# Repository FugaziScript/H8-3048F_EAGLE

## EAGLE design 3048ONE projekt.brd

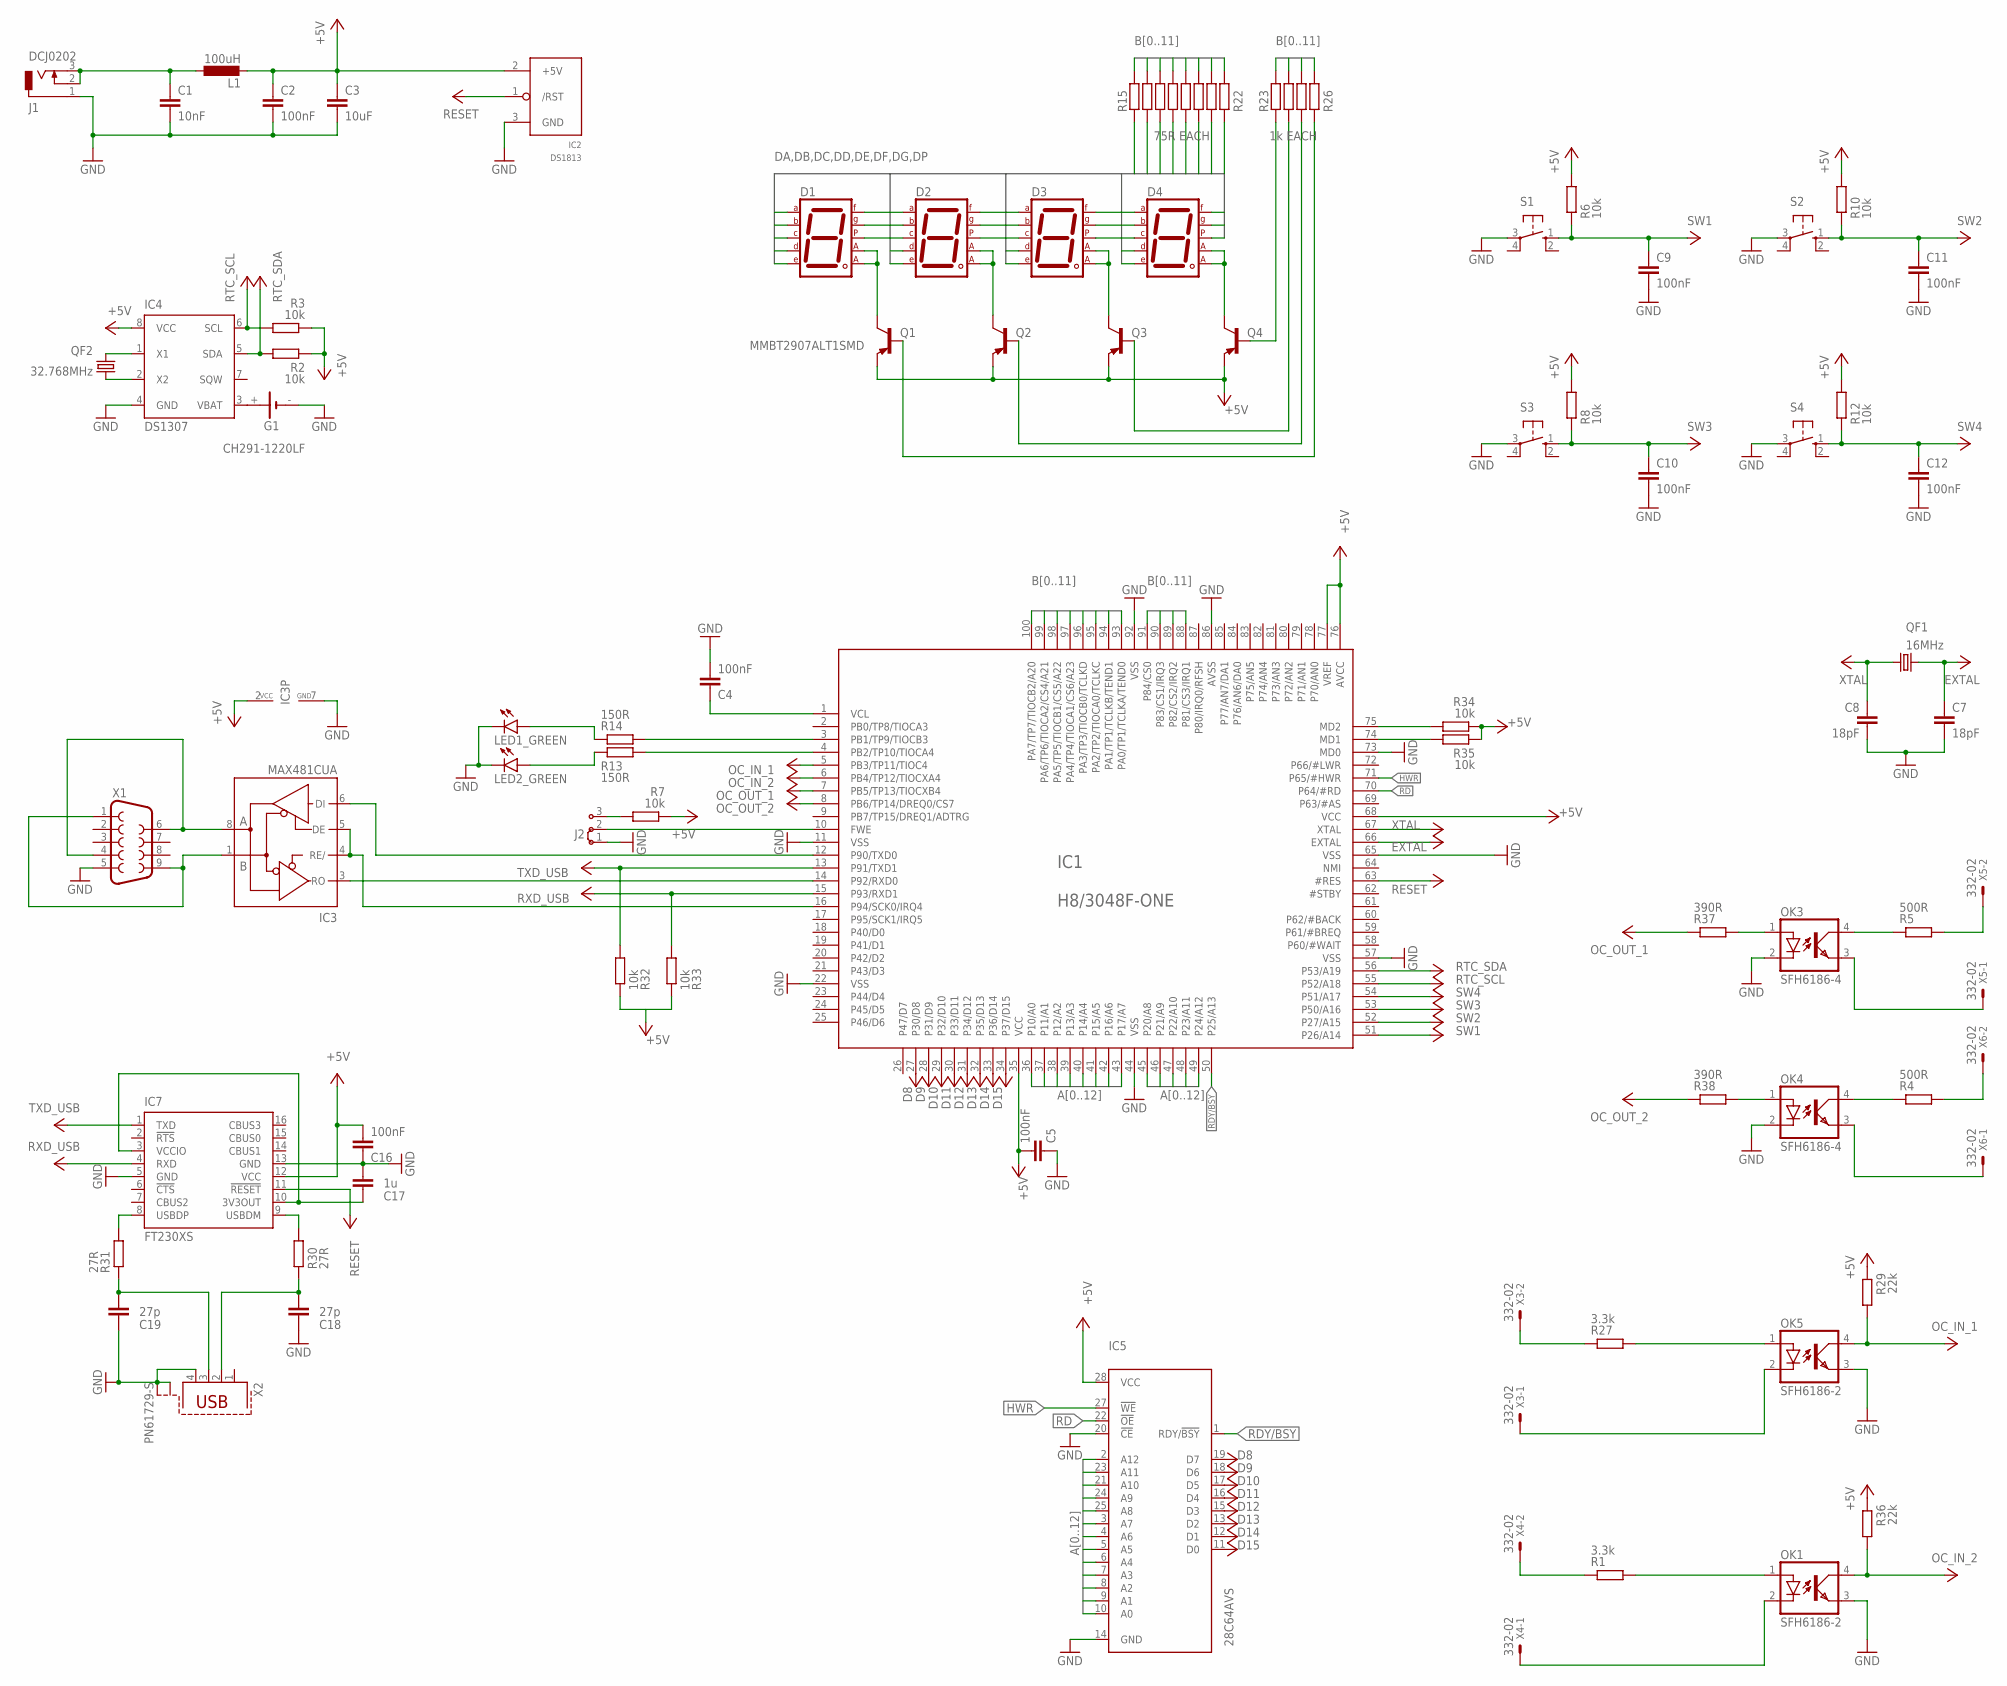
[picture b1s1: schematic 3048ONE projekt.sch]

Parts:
C1: 10nF; C0805
C2, C4, C5, C9, C10, C11, C12, C16: 100nF; C0805
C3: 10uF; C0805
C7, C8: 18pF; C0805
C17: 1u; C0805
C18, C19: 27p; C0805
D1, D2, D3, D4: 7SEG-CA; 7SEG-13
G1: CH291-1220LF
IC1: H8/3048F-ONE; TQFP100-16X16
IC2: DS1813; TO-92
IC3: MAX481CUA; UMAX8
IC4: DS1307; DIL08
IC5: 28C64AVS; VSOP28-8X13
IC7: FT230XS; SSOP16
J1: DCJ0202
J2: J2X2MM; 04C
L1: 100uH; PIS2816
LED1_GREEN, LED2_GREEN: LED3MM
OK1, OK5: SFH6186-2; SMD4-7
OK3, OK4: SFH6186-4; SMD4-7
Q1, Q2, Q3, Q4: MMBT2907ALT1SMD; SOT23-BEC
QF1: 16MHz; CTS406
QF2: 32.768MHz; CTS406
R1, R27: 3.3k; M0805
R2, R3, R6, R7, R8, R10, R12, R32, R33, R34, R35: 10k; M0805
R4, R5: 500R; M0805
R13, R14, R15, R16, R17, R18, R19, R20, R21, R23, R24, R25: 150R; M0805
R22: 75R EACH; M0805
R26: 1k EACH; M0805
R29, R36: 22k; M0805
R30, R31: 27R; M0805
R37, R38: 390R; M0805
S1, S2, S3, S4: 40-XX; B3F-40XX
X1: F09HP
X2: PN61729-S
X3, X4, X5, X6: 332-02

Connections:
+5V: C2.1, C3.1, C5.2, C16.2, IC1.35 (VCC), IC1.68 (VCC), IC1.76 (AVCC), IC1.77 (VREF), IC2.2 (+5V), IC3.2 (VCC), IC4.8 (VCC), IC5.28 (VCC), IC7.12 (VCC), L1.2, Q1.E, Q2.E, Q3.E, Q4.E, R2.1, R3.1, R6.2, R7.1, R8.2, R10.2, R12.2, R29.1, R34.1, R35.1, R36.1
A0: IC1.38 (P12/A2), IC5.10 (A0)
A1: IC1.37 (P11/A1), IC5.9 (A1)
A2: IC1.36 (P10/A0), IC5.8 (A2)
A3: IC1.49 (P24/A12), IC5.7 (A3)
A4: IC1.48 (P23/A11), IC5.6 (A4)
A5: IC1.47 (P22/A10), IC5.5 (A5)
A6: IC1.46 (P21/A9), IC5.4 (A6)
A7: IC1.45 (P20/A8), IC5.3 (A7)
A8: IC1.42 (P16/A6), IC5.25 (A8)
A9: IC1.41 (P15/A5), IC5.24 (A9)
A10: IC1.39 (P13/A3), IC5.21 (A10)
A11: IC1.40 (P14/A4), IC5.23 (A11)
A12: IC1.43 (P17/A7), IC5.2 (A12)
B0: IC1.100 (PA7/TP7/TIOCB2/A20), R15.1
B1: IC1.99 (PA6/TP6/TIOCA2/CS4/A21), R16.1
B2: IC1.98 (PA5/TP5/TIOCB1/CS5/A22), R17.1
B3: IC1.97 (PA4/TP4/TIOCA1/CS6/A23), R18.1
B4: IC1.96 (PA3/TP3/TIOCB0/TCLKD), R19.1
B5: IC1.95 (PA2/TP2/TIOCA0/TCLKC), R20.1
B6: IC1.94 (PA1/TP1/TCLKB/TEND1), R21.1
B7: IC1.93 (PA0/TP1/TCLKA/TEND0), R22.1
B8: IC1.91 (P84/CS0), R23.1
B9: IC1.90 (P83/CS1/IRQ3), R24.1
B10: IC1.89 (P82/CS2/IRQ2), R25.1
B11: IC1.88 (P81/CS3/IRQ1), R26.1
D8: IC1.27 (P30/D8), IC5.19 (D7)
D9: IC1.28 (P31/D9), IC5.18 (D6)
D10: IC1.29 (P32/D10), IC5.17 (D5)
D11: IC1.30 (P33/D11), IC5.16 (D4)
D12: IC1.31 (P34/D12), IC5.15 (D3)
D13: IC1.32 (P35/D13), IC5.13 (D2)
D14: IC1.33 (P36/D14), IC5.12 (D1)
D15: IC1.34 (P37/D15), IC5.11 (D0)
DA: D1.7 (A), D2.7 (A), D3.7 (A), D4.7 (A), R19.2
DB: D1.6 (B), D2.6 (B), D3.6 (B), D4.6 (B), R21.2
DC: D1.4 (C), D2.4 (C), D3.4 (C), D4.4 (C), R20.2
DD: D1.2 (D), D2.2 (D), D3.2 (D), D4.2 (D), R18.2
DE: D1.1 (E), D2.1 (E), D3.1 (E), D4.1 (E), R17.2
DF: D1.9 (F), D2.9 (F), D3.9 (F), D4.9 (F), R16.2
DG: D1.10 (G), D2.10 (G), D3.10 (G), D4.10 (G), R15.2
DP: D1.5 (DP), D2.5 (DP), D3.5 (DP), D4.5 (DP), R22.2
EXTAL: C7.1, IC1.66 (EXTAL), QF1.3 (2)
GND: C1.2, C2.2, C3.2, C4.2, C5.1, C7.2, C8.2, C9.2, C10.2, C11.2, C12.2, C16.1, C17.2, C18.1, C19.1, G1.-, IC1.11 (VSS), IC1.22 (VSS), IC1.44 (VSS), IC1.57 (VSS), IC1.65 (VSS), IC1.73 (MD0), IC1.86 (AVSS), IC1.92 (VSS), IC2.3 (GND), IC3.7 (GND), IC4.4 (GND), IC5.14 (GND), IC5.20 (!CE), IC7.5 (GND), IC7.13 (GND), J1.1, J2.1, LED1_GREEN.K (C), LED2_GREEN.K (C), OK1.3 (EMIT), OK3.2 (C), OK4.2 (C), OK5.3 (EMIT), S1.3, S2.3, S3.3, S4.3, X1.5, X2.4, X2.S1, X2.S2
HWR: IC1.71 (P65/#HWR), IC5.27 (!WE)
unnamed: IC1.10 (FWE), J2.2
unnamed: C1.1, J1.2, J1.3, L1.1
unnamed: IC3.1 (B), X1.1, X1.9
unnamed: IC3.8 (A), X1.4, X1.6
unnamed: IC1.14 (P92/RXD0), IC3.3 (RO)
unnamed: IC4.1 (X1), QF2.3 (2)
unnamed: IC1.12 (P90/TXD0), IC3.6 (DI)
unnamed: IC4.2 (X2), QF2.1
unnamed: G1.+, IC4.3 (VBAT)
unnamed: OK5.2 (C), X3.1
unnamed: IC1.16 (P94/SCK0/IRQ4), IC3.4 (RE/), IC3.5 (DE)
unnamed: OK1.2 (C), X4.1
unnamed: C4.1, IC1.1 (VCL)
unnamed: OK3.4 (COL), R5.1
unnamed: OK1.1 (A), R1.2
unnamed: OK4.4 (COL), R4.1
unnamed: IC1.75 (MD2), R34.2
unnamed: J2.3, R7.2
unnamed: IC1.74 (MD1), R35.2
unnamed: LED1_GREEN.A, R14.1
unnamed: LED2_GREEN.A, R13.1
unnamed: IC1.3 (PB1/TP9/TIOCB3), R14.2
unnamed: IC1.4 (PB2/TP10/TIOCA4), R13.2
unnamed: D1.3 (CA1), D1.8 (CA2), Q1.C
unnamed: D2.3 (CA1), D2.8 (CA2), Q2.C
unnamed: D3.3 (CA1), D3.8 (CA2), Q3.C
unnamed: D4.3 (CA1), D4.8 (CA2), Q4.C
unnamed: Q4.B, R23.2
unnamed: Q3.B, R24.2
unnamed: Q2.B, R25.2
unnamed: Q1.B, R26.2
unnamed: OK5.1 (A), R27.2
unnamed: R32.1, R33.1
unnamed: IC7.9 (USBDM), R30.1
unnamed: C19.2, R31.1, X2.3
unnamed: C18.2, R30.2, X2.2
unnamed: C17.1, IC7.3 (VCCIO), IC7.10 (3V3OUT)
unnamed: IC7.8 (USBDP), R31.2
unnamed: R27.1, X3.2
unnamed: R1.1, X4.2
unnamed: OK3.1 (A), R37.2
unnamed: R4.2, X6.2
unnamed: OK3.3 (EMIT), X5.1
unnamed: OK4.1 (A), R38.2
unnamed: OK4.3 (EMIT), X6.1
unnamed: R5.2, X5.2
OC_IN_2: IC1.6 (PB4/TP12/TIOCXA4), OK1.4 (COL), R36.2
OC_OIN_1: IC1.5 (PB3/TP11/TIOC4), OK5.4 (COL), R29.2
OC_OUT_1: IC1.7 (PB5/TP13/TIOCXB4), R37.1
OC_OUT_2: IC1.8 (PB6/TP14/DREQ0/CS7), R38.1
RD: IC1.70 (P64/#RD), IC5.22 (!OE)
RDY/BSY: IC1.50 (P25/A13), IC5.1 (RDY/!BSY)
RESET: IC1.63 (#RES), IC2.1 (/RST), IC7.11 (!RESET)
RTC_SCL: IC1.55 (P52/A18), IC4.6 (SCL), R3.2
RTC_SDA: IC1.56 (P53/A19), IC4.5 (SDA), R2.2
RXD_USB: IC1.15 (P93/RXD1), IC7.4 (RXD), R33.2
SW1: C9.1, IC1.51 (P26/A14), R6.1, S1.1 (S)
SW2: C11.1, IC1.52 (P27/A15), R10.1, S2.1 (S)
SW3: C10.1, IC1.53 (P50/A16), R8.1, S3.1 (S)
SW4: C12.1, IC1.54 (P51/A17), R12.1, S4.1 (S)
TXD_USB: IC1.13 (P91/TXD1), IC7.1 (TXD), R32.2
XTAL: C8.1, IC1.67 (XTAL), QF1.1

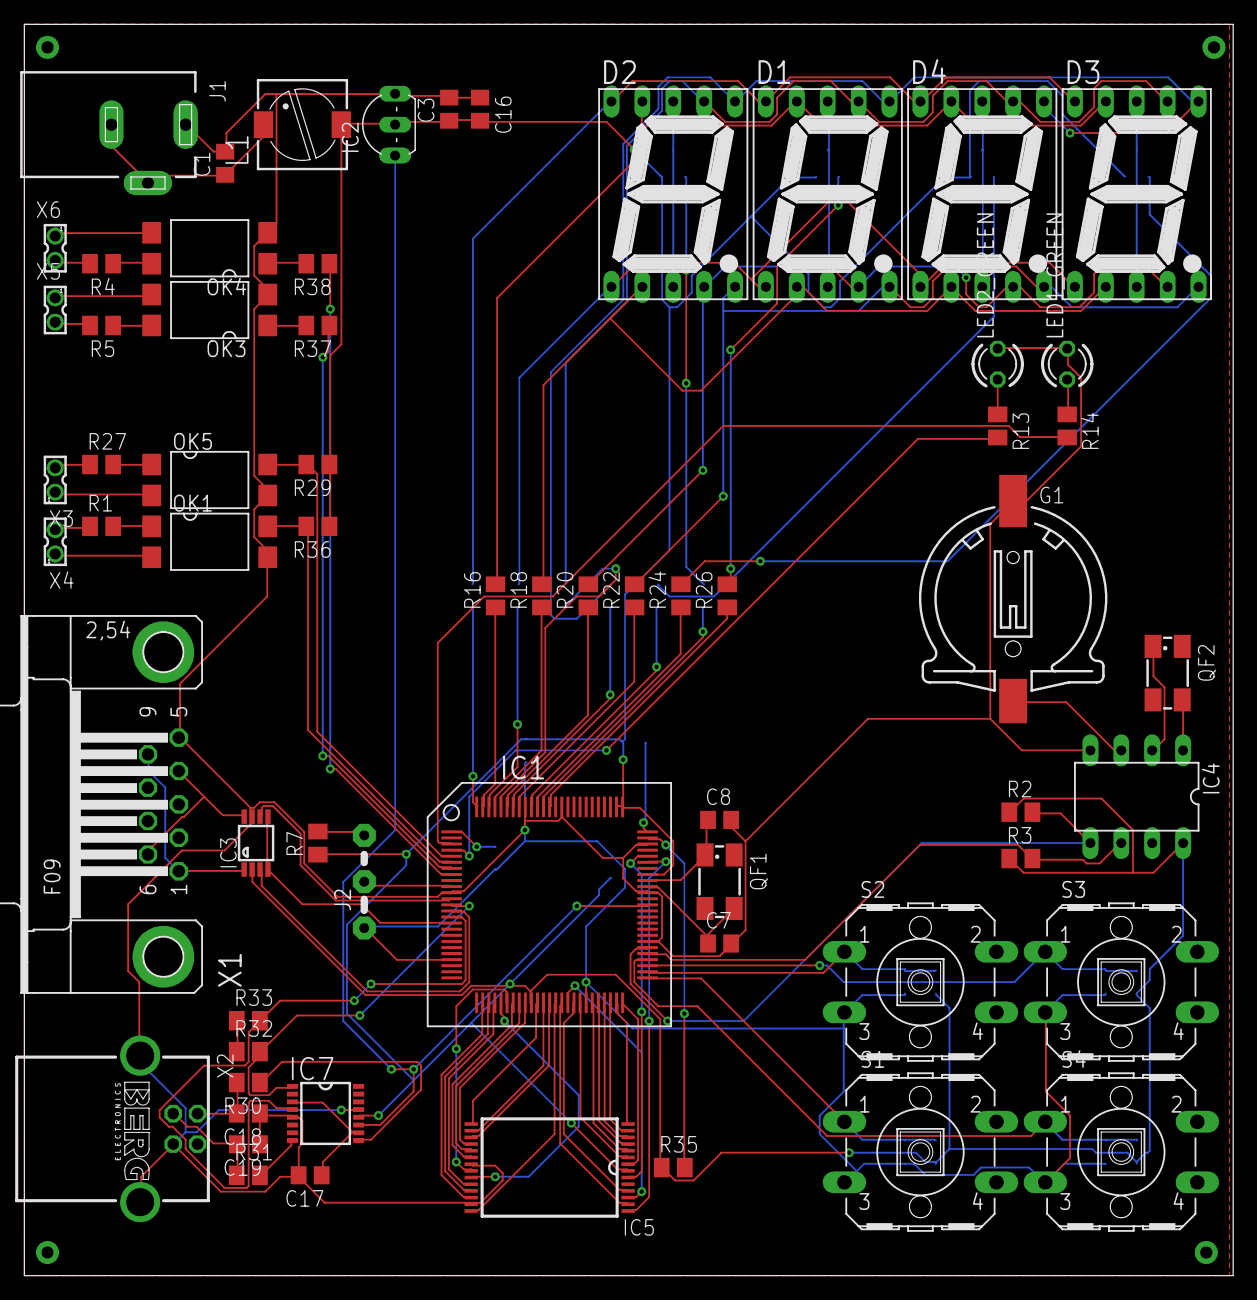
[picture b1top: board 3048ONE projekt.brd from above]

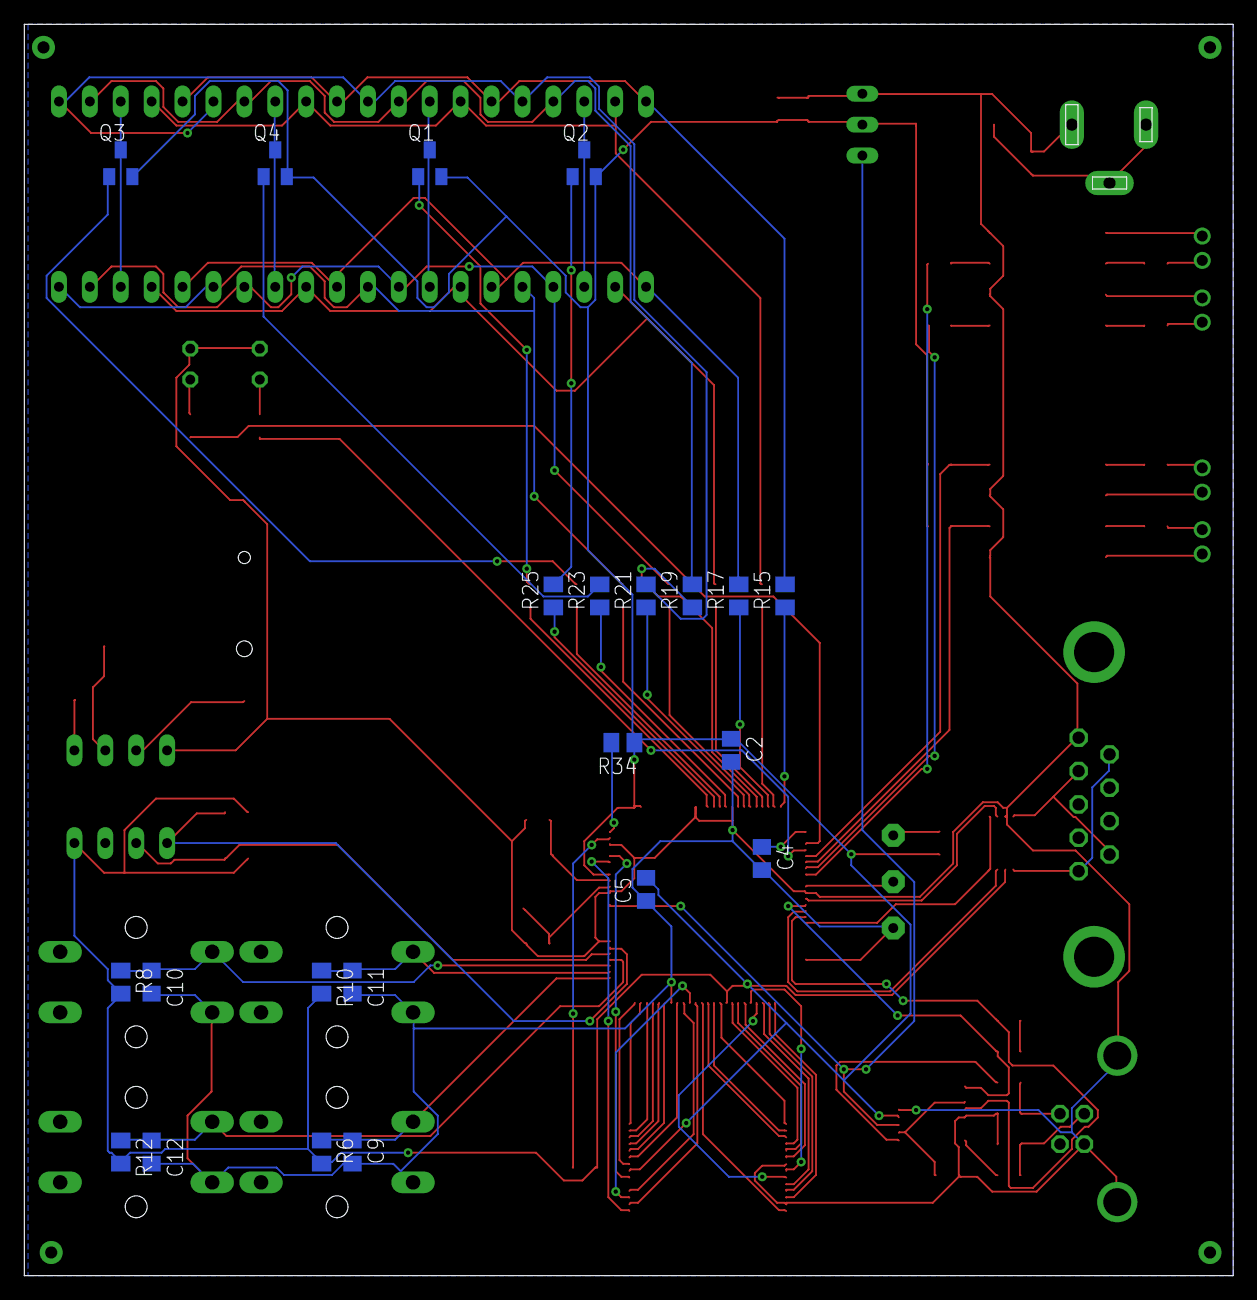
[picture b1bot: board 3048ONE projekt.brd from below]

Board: 2 copper layers, 99.4 x 102.9 mm, 86 parts (22 on the bottom side), 107 nets.
